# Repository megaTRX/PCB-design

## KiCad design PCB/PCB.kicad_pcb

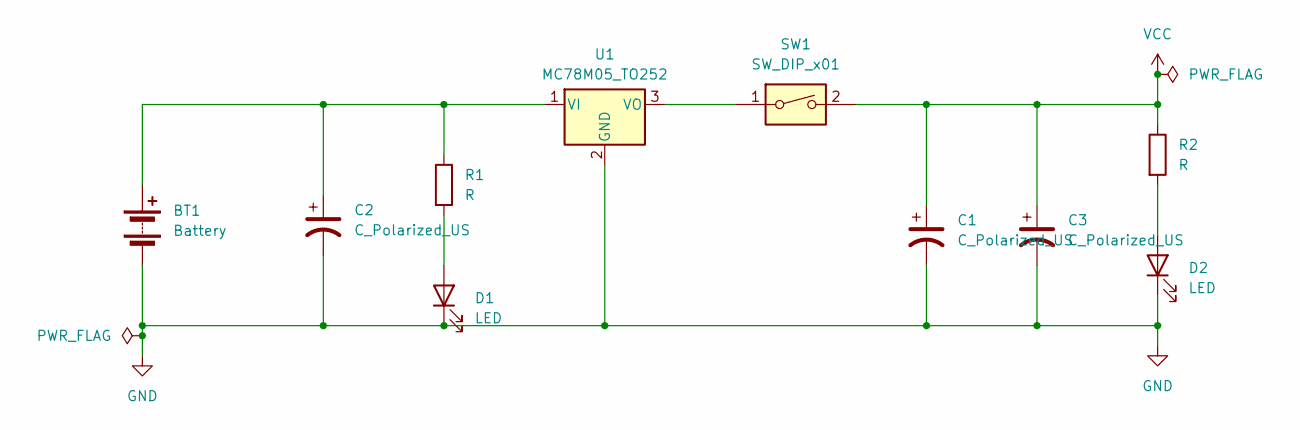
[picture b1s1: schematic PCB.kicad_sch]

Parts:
BT1: Battery; BatteryHolder_Keystone_2468_2xAAA
C1, C2, C3: C_Polarized_US; CP_Axial_L10.0mm_D4.5mm_P15.00mm_Horizontal
D1, D2: LED; LED_D3.0mm
R1, R2: R; R_Axial_DIN0204_L3.6mm_D1.6mm_P2.54mm_Vertical
SW1: SW_DIP_x01; SW_DIP_SPSTx01_Slide_9.78x4.72mm_W7.62mm_P2.54mm
U1: MC78M05_TO252; TO-252-2

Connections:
GND: BT1.2 (-), C1.2, C2.2, C3.2, D1.1 (K), D2.1 (K), U1.2 (GND)
unnamed: BT1.1 (+), C2.1, R1.1, U1.1 (VI)
unnamed: D1.2 (A), R1.2
unnamed: D2.2 (A), R2.2
unnamed: SW1.1, U1.3 (VO)
VCC: C1.1, C3.1, R2.1, SW1.2

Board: 2 copper layers, 10 parts (0 on the bottom side), 6 nets, no tracks yet.

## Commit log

2026-01-04 마이크로컨트롤러 보드의 전원회로도 PCB설계
